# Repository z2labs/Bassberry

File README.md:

<p align="center">
  <b>A pocketable hi-fi 2.1 Bluetooth / Wi-Fi speaker built around any Raspberry Pi.</b><br>
  Cheap, easy-to-source parts · 3S 18650 battery from recycled cells · 3D-printed acoustic enclosure · fully open source
</p>

> **Status: rev 0.2 hardware in progress.** Acoustic design and simulation done. KiCad 10 schematic complete, with a HAT+ ID EEPROM so the Pi recognises the board. PCB placed by function and routed with srouter. A 4-layer digital twin verifies it against the datasheets. See [`hardware/`](hardware/).
> Everything here will change - issues and ideas are very welcome.

---

## Why

Raspberry Pi speaker HATs are either tiny mono buzzers or bare amplifier boards that leave the hard part to you: drivers, enclosure, power, battery.
Bassberry is the whole thing: a motherboard the Pi plugs into **upside down**, a DSP class-D 2.1 amplifier, USB-C PD charging, a clip-in 3S 18650 pack, and a simulated acoustic enclosure you can print at home.

It is the successor of [rfsparkling/RPi_Speaker](https://github.com/rfsparkling/RPi_Speaker) (an LM386 + GPIO-PWM board from 2016), redone properly.

## Highlights

| | |
|---|---|
| **Audio** | 2.1 channel, I2S digital all the way, 2× TI TAS5805M class-D with on-chip DSP (EQ, crossover, DRC) |
| **Drivers** | 2× 2" full-range satellites (sealed) + 1× 3.5" long-throw sub, down-firing, with 2 opposed passive radiators |
| **Response** | f₋₃ ≈ **64 Hz**, ±0.8 dB 100 Hz – 1 kHz (simulated, with DSP) |
| **Output** | ≈ **85 dB** broadband, **87 dB** @ 100 Hz, **94–97 dB** midrange @ 1 m (simulated) |
| **Host** | Every 40-pin Raspberry Pi: 1 A+/B+, 2, 3, 4, 5, Zero / Zero W / Zero 2 W - detected as a **HAT+** (ID EEPROM loads the overlay) |
| **Cooling** | Pi mounted upside down; SoC sits on an aluminium pedestal + gap pad into a 4-layer GND via field. No fan. |
| **Power** | USB-C PD in (5–20 V), 3S Li-ion buck-boost charging, 5.1 V / 5 A for the Pi, optional 18 V rail for the sub amp |
| **Battery** | 3× 18650 in snap-in holders with spring metal contacts - new or harvested cells, with balancing and reverse-cell indication |
| **UI** | 1.3" I2C OLED, power / BT / play / vol− / vol+ buttons, rotary encoder for menus (internet radio, EQ, sources) |
| **Size** | 230 × 120 × 140 mm |

## Renders

| Exterior | Rear (passive radiator, ports) |
|---|---|
|  |  |
| **Interior: acoustic chambers** | **Exploded** |
|  |  |
| **Top controls** | **Motherboard: upside-down Pi + 3S pack** |
|  |  |

Renders are generated from code with Blender Cycles: [`render/render.py`](render/render.py).

### PCB rev 0.2 (KiCad 10, routed with srouter)

| Top (Pi socket face-down, 3× 18650, lid controls) | Bottom (amplifiers, charger, buck, supervisor) |
|---|---|
|  |  |

180 × 110 mm, 4 layers. DRC 0 errors / 0 unconnected / 0 schematic-parity issues; digital twin layers 1-4 all PASS
(netlist vs datasheets, Pi plugged in face-down, copper ampacity incl. pours and vias, mechanics). Details in
[`hardware/README.md`](hardware/README.md).
Orange = sealed satellite chambers (0.20 l each), green = sub chamber (1.5 l) tuned by two opposed passive radiators.

## Acoustics

* **Satellites:** 2× 2" full-range (reference: Dayton CE54N-4) in 0.20 l sealed chambers, crossed at 180 Hz LR4.
* **Sub:** 3.5" long-throw (reference: Dayton ND91-4, Xmax 4.6 mm), down-firing, 1.5 l, with 2× 2.5" passive radiators on the side walls facing each other, so their momentum cancels and the box does not walk at high bass. Tuned to 57 Hz.
* **DSP (in the TAS5805M):** LR4 crossover, Linkwitz transform on the satellites, baffle-step compensation, subsonic filter, bass EQ, dynamic range control.
* Full lumped-element model, max-SPL / excursion limits and a driver comparison: [`docs/acoustics.md`](docs/acoustics.md) and [`acoustics/`](acoustics/).
  Plug in your own driver's T/S parameters and re-run in seconds.

## Architecture

```mermaid
flowchart LR
  USBC["USB-C PD<br/>5-20 V"] --> CHG["PD sink + 3S<br/>buck-boost charger"]
  CHG <--> BAT["3S 18650<br/>clip-in pack + BMS"]
  BAT --> BUCK["5.1 V / 5 A buck"] --> PI["Raspberry Pi<br/>(upside down)"]
  BAT --> AMP1["TAS5805M #1<br/>stereo BTL"]
  BAT --> BOOST["18 V boost<br/>(optional)"] --> AMP2["TAS5805M #2<br/>sub PBTL"]
  PI -- I2S --> AMP1 & AMP2
  PI -- I2C --> AMP1 & AMP2 & OLED["1.3&quot; OLED"]
  MCU["Supervisor MCU<br/>buttons · encoder · power latch"] -- I2C/IRQ --> PI
  MCU --> CHG
  AMP1 --> SAT["2× 2&quot; satellites"]
  AMP2 --> SUB["3.5&quot; sub + 2× PR"]
  USBC -- D+/D− --> UART["USB-UART"] --> PI
```

Details, pinout plan and power budget: [`docs/architecture.md`](docs/architecture.md).

## Built from cheap, common parts

The design rule is simple: **everything should be orderable from LCSC / AliExpress / your local electronics shop**, no exotic parts.
Amplifiers, charger, supervisor MCU, OLED, encoder and battery clips are all mass-market parts. Drivers come in two tiers:
reference drivers with published Thiele-Small data (what the simulation uses), or generic drivers that fit the same footprints, which you can measure and drop into the model.
See [`docs/bom.md`](docs/bom.md).

## Battery: recycled cells welcome

The pack is three 18650 cells in snap-in metal clips, so you can use new cells or ones harvested from old laptop packs.
Please read [`docs/battery.md`](docs/battery.md) first: matching, testing and the protections on the board.

## Roadmap

- [x] Concept, architecture, acoustic design and simulation
- [x] Schematic (KiCad 10, generated from [`hardware/tools`](hardware/tools))
- [ ] PCB layout, 4-layer, Pi thermal pedestal (rev 0.2: placed + routed, DRC / twin closure in progress)
- [ ] 3D-printable enclosure (STEP + STL), gaskets, damping
- [ ] Linux: dual TAS5805M 2.1 sound card, DSP profiles, supervisor daemon, OLED menu
- [ ] Prototype measurements vs simulation
- [ ] Build guide

## Repository layout

```
acoustics/   lumped-element simulation, plots, driver comparison
docs/        architecture, acoustics, BOM, battery guide, images
render/      Blender (bpy) script that generates the renders
tools/       helper scripts (banner, ...)
hardware/    KiCad 10 project + Python generators
enclosure/   CAD / STL (coming)
software/    Linux drivers, DSP profiles, UI (coming)
```

## License

* Hardware (`hardware/`, `enclosure/`): [CERN-OHL-S-2.0](LICENSES/CERN-OHL-S-2.0.txt)
* Software and scripts: [MIT](LICENSES/MIT.txt)
* Documentation and images: [CC-BY-SA-4.0](LICENSES/CC-BY-SA-4.0.txt)

Made by [Z2Labs](https://github.com/z2labs) in Budapest.

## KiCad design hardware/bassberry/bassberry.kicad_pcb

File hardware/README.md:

# Hardware - Bassberry motherboard (KiCad 10)

**Status: rev 0.2 (branch `feat/rev02-layout`) - HAT+ EEPROM, back-power diode, 18650 holders, functional placement, srouter routing, digital twin.**

Open `bassberry/bassberry.kicad_pro` in KiCad 10. A PDF of the schematic is in [`bassberry/bassberry_sch.pdf`](bassberry/bassberry_sch.pdf).

## Sheets

| Sheet | Content |
|---|---|
| `pi.kicad_sch` | 40-pin socket for a **face-down** Raspberry Pi (B+/2/3/4/5/Zero), I2S series termination, HAT+ ID EEPROM (CAT24C32 @ 0x50, WP jumper), back-power ideal diode |
| `audio.kicad_sch` | 2x TI TAS5805M: U201 stereo BTL (satellites, PVDD = VBAT), U202 PBTL (sub, PVDD_SUB), LC output filters, speaker connectors |
| `power.kicad_sch` | USB-C, Injoinic IP2366 PD3.1 3S buck-boost charger (30 W, 4.2 V/cell), TPS565208 5.1 V / 5 A Pi buck, optional MT3608 ~17 V sub boost, HT7533 LDOs |
| `battery.kicad_sch` | 3x 18650 in MYOUNG BH-18650-B1BA002 SMT holders (Keystone 1042 clone), off-the-shelf 3S BMS module (B-, B1, B2, B+, P-), reverse-cell LEDs, 10 A fuse, NTC |
| `ui.kicad_sch` | CH32V003 supervisor (power latch, buttons, encoder, VBAT sense, I2C slave to the Pi), OLED header, CH340C USB console |

Reference designators are numbered per sheet: 1xx Pi, 2xx audio, 3xx power, 4xx battery, 5xx UI.

## Board

* 180 x 110 mm, 4 layers, 1.6 mm. Layer roles as in srouter's rev-B3 flow: **F.Cu** signals + GND pour, **In1.Cu** signals
  (power stays on the outer layers), **In2.Cu** solid GND, **B.Cu** parts + signals + GND pour. Netclass 0.15 mm / 0.2 mm, via 0.6/0.3 mm.
* Top: face-down Pi (fitted to the Pi 4/5 hole pattern, ports over the open rear-left corner), three 18650 holders front-to-back
  with alternating polarity (series links 20 mm), USB-C at the rear, buttons / EC11 encoder / OLED socket in the front strip.
* Bottom: every other part, placed by function: each passive next to the pin it serves (`pcb_build.py`).
* Pi SoC thermal pad: covers the Pi 4 **and** the Pi 5 SoC lid (from the mechanical drawings), exposed copper both sides,
  0.3 mm GND via field, two M2.5 bolts for the aluminium pedestal. Copper keep-out under the Pi 4/5 Wi-Fi antenna corner.

## Regenerating (Windows, KiCad 10)

```powershell
powershell -File hardware\tools\regen_sch.ps1                       # schematic, ERC, netlist
& $py hardware\tools\pcb_build.py                                   # outline, placement, zones -> bassberry_placed.kicad_pcb
& $py hardware\tools\route.py                                       # srouter: escape gate, trunks + 3 passes, fatten
powershell -File hardware\tools\postroute.ps1                       # track_tidy, fill, gnd_stitch, via_rescue, stitch_audit,
                                                                     # silk_dfm, DRC --schematic-parity, digital twin 1-4
```

Routing follows `srouter/docs/USAGE.md`: GND is never routed (In2 plane + F/B pours, stitched afterwards).
* **Pass 0 (trunks)** - srouter gives a net one width that must fit its smallest pad, so a battery rail that also touches a
  0.3 mm amplifier pin would be 0.2 mm end to end. `route.py` therefore splits each high-current net on a scratch copy:
  the small pads go to a dummy net, and srouter joins only the big pads (holders, fuse, 2512 links, inductors, MOSFET tabs,
  connectors) at the widest width they allow (up to 1.6 mm). The later passes join the small pads to that trunk at their own
  width: the neck-down happens only in the last millimetres before a fine-pitch pin.
* **Pass 1a** - the rest of the high-current nets alone, on the outer copper only (In1 closed: 0.5 oz inner copper would need 3x the
  width), vias strongly avoided. srouter routes a net with one width that has to fit its smallest pad, so `fatten.py` then
  widens that copper wherever the clearance allows (necking only next to small pads, keeping a 0.5 mm escape lane around
  every foreign pad) and adds parallel vias at its layer changes.
* **Pass 1b** - everything that escapes from between power pins (the IP2366 QFN, the amp bootstrap pins) and the 3V3 rails.
* **Pass 2** - I2S, I2C, USB D+/D- (crossover under the receptacle pre-routed), HAT ID, every other Pi header net.
* **Pass 3** - the rest.
* **Post** (`postroute.ps1`, the USAGE.md order): track_tidy, `power_pour.py` (a priority-5 copper pour hugging every
  high-current track on F.Cu, In1.Cu and B.Cu, filled only into free space, plus ceil(I / 1.5 A) parallel vias at every
  layer change of a high-current net), zone fill, gnd_stitch, via_rescue, stitch_audit, silk_dfm, zone refill, DRC with
  schematic parity, digital twin 1-4. `full_flow.ps1` runs everything unattended.
* Gates: `escape_probe.py` (no pad walled in before routing), the pre-route twin layers 1/2/4; `full_flow.ps1` stops on any failure.
* Repairs: `tidy_guard.py` re-joins what srouter's track_tidy pulls apart (pads, track pieces, lost layer changes) and drops dangling stubs;
  GND pins with no room for a via get one between the pin rows (0.45/0.2 mm) or a short link to the nearest GND.

## Digital twin

`hardware/twin/` - four layers, spec written only from datasheets and the Raspberry Pi documents, each with injected-fault
self-tests. See [`twin/README.md`](twin/README.md).

## Result (rev 0.2, `hardware/bassberry/route/`)

| Check | Result |
|---|---|
| ERC | 2 expected errors only (TAS5805M PBTL output pairing, as in the TI datasheet) |
| Routing | every net routed by srouter (trunk pass, 3 passes, automatic rip-up and reroute for nets left over) |
| DRC (`--schematic-parity --severity-all`) | **0 errors, 0 unconnected, 0 parity**; 152 warnings: 122 `lib_footprint_mismatch` (silk_dfm moved/cut silkscreen inside the footprints), 29 silkscreen cosmetics, 1 copper sliver |
| Twin layer 1 (netlist vs source documents) | 170 PASS, 10 WARN (physical checks + accepted deviations), 0 FAIL; 16/16 injected faults caught |
| Twin layer 2 (Pi 4/5 plugged in face-down) | 7 + 31 PASS; 2/2 injected faults caught |
| Twin layer 3 (copper ampacity, set-points, LDO) | 36 PASS, 0 FAIL; 2/2 injected faults caught |
| Twin layer 4 (mechanics) | 37 PASS; 4/4 injected faults caught |

How the power copper was made to pass layer 3 (all automatic, `power_pour.py`): corridor pours per high-current net on
F.Cu / In1.Cu / B.Cu splitting the room between neighbouring nets, a **+BATT plane on In1.Cu** fed by taps from every
+BATT pad, In1 copies of the battery-link pours (joined by the holder through-hole contacts), and vias grown to 1.0/0.5 mm
or doubled until each layer change carries its current. The buck converter is turned so its SW pin points straight at the
inductor, the ZVD PFET so its source pins face the Pi 5 V pins.

## Known open items (rev 0.2)

- [ ] ERC: 2 expected errors - TAS5805M PBTL pre-filter output pairing (OUT_A+/OUT_A-, OUT_B+/OUT_B-), exactly as in TI's datasheet fig. "MONO (PBTL) Systems".
- [ ] Confirm the Pi antenna keep-out on a real Pi 4 / Pi 5 / Pi 3B+.
- [ ] CH340C supply current from the current WCH datasheet (the LDO dissipation check at a 20 V PD contract uses 15 mA).
- [ ] TDSON MOSFETs: pick the final cheap part (30-40 V, ~5 mOhm, JEDEC SO-8FL pin-out).
- [ ] Device tree overlay and DSP profiles (`software/overlay`, draft).

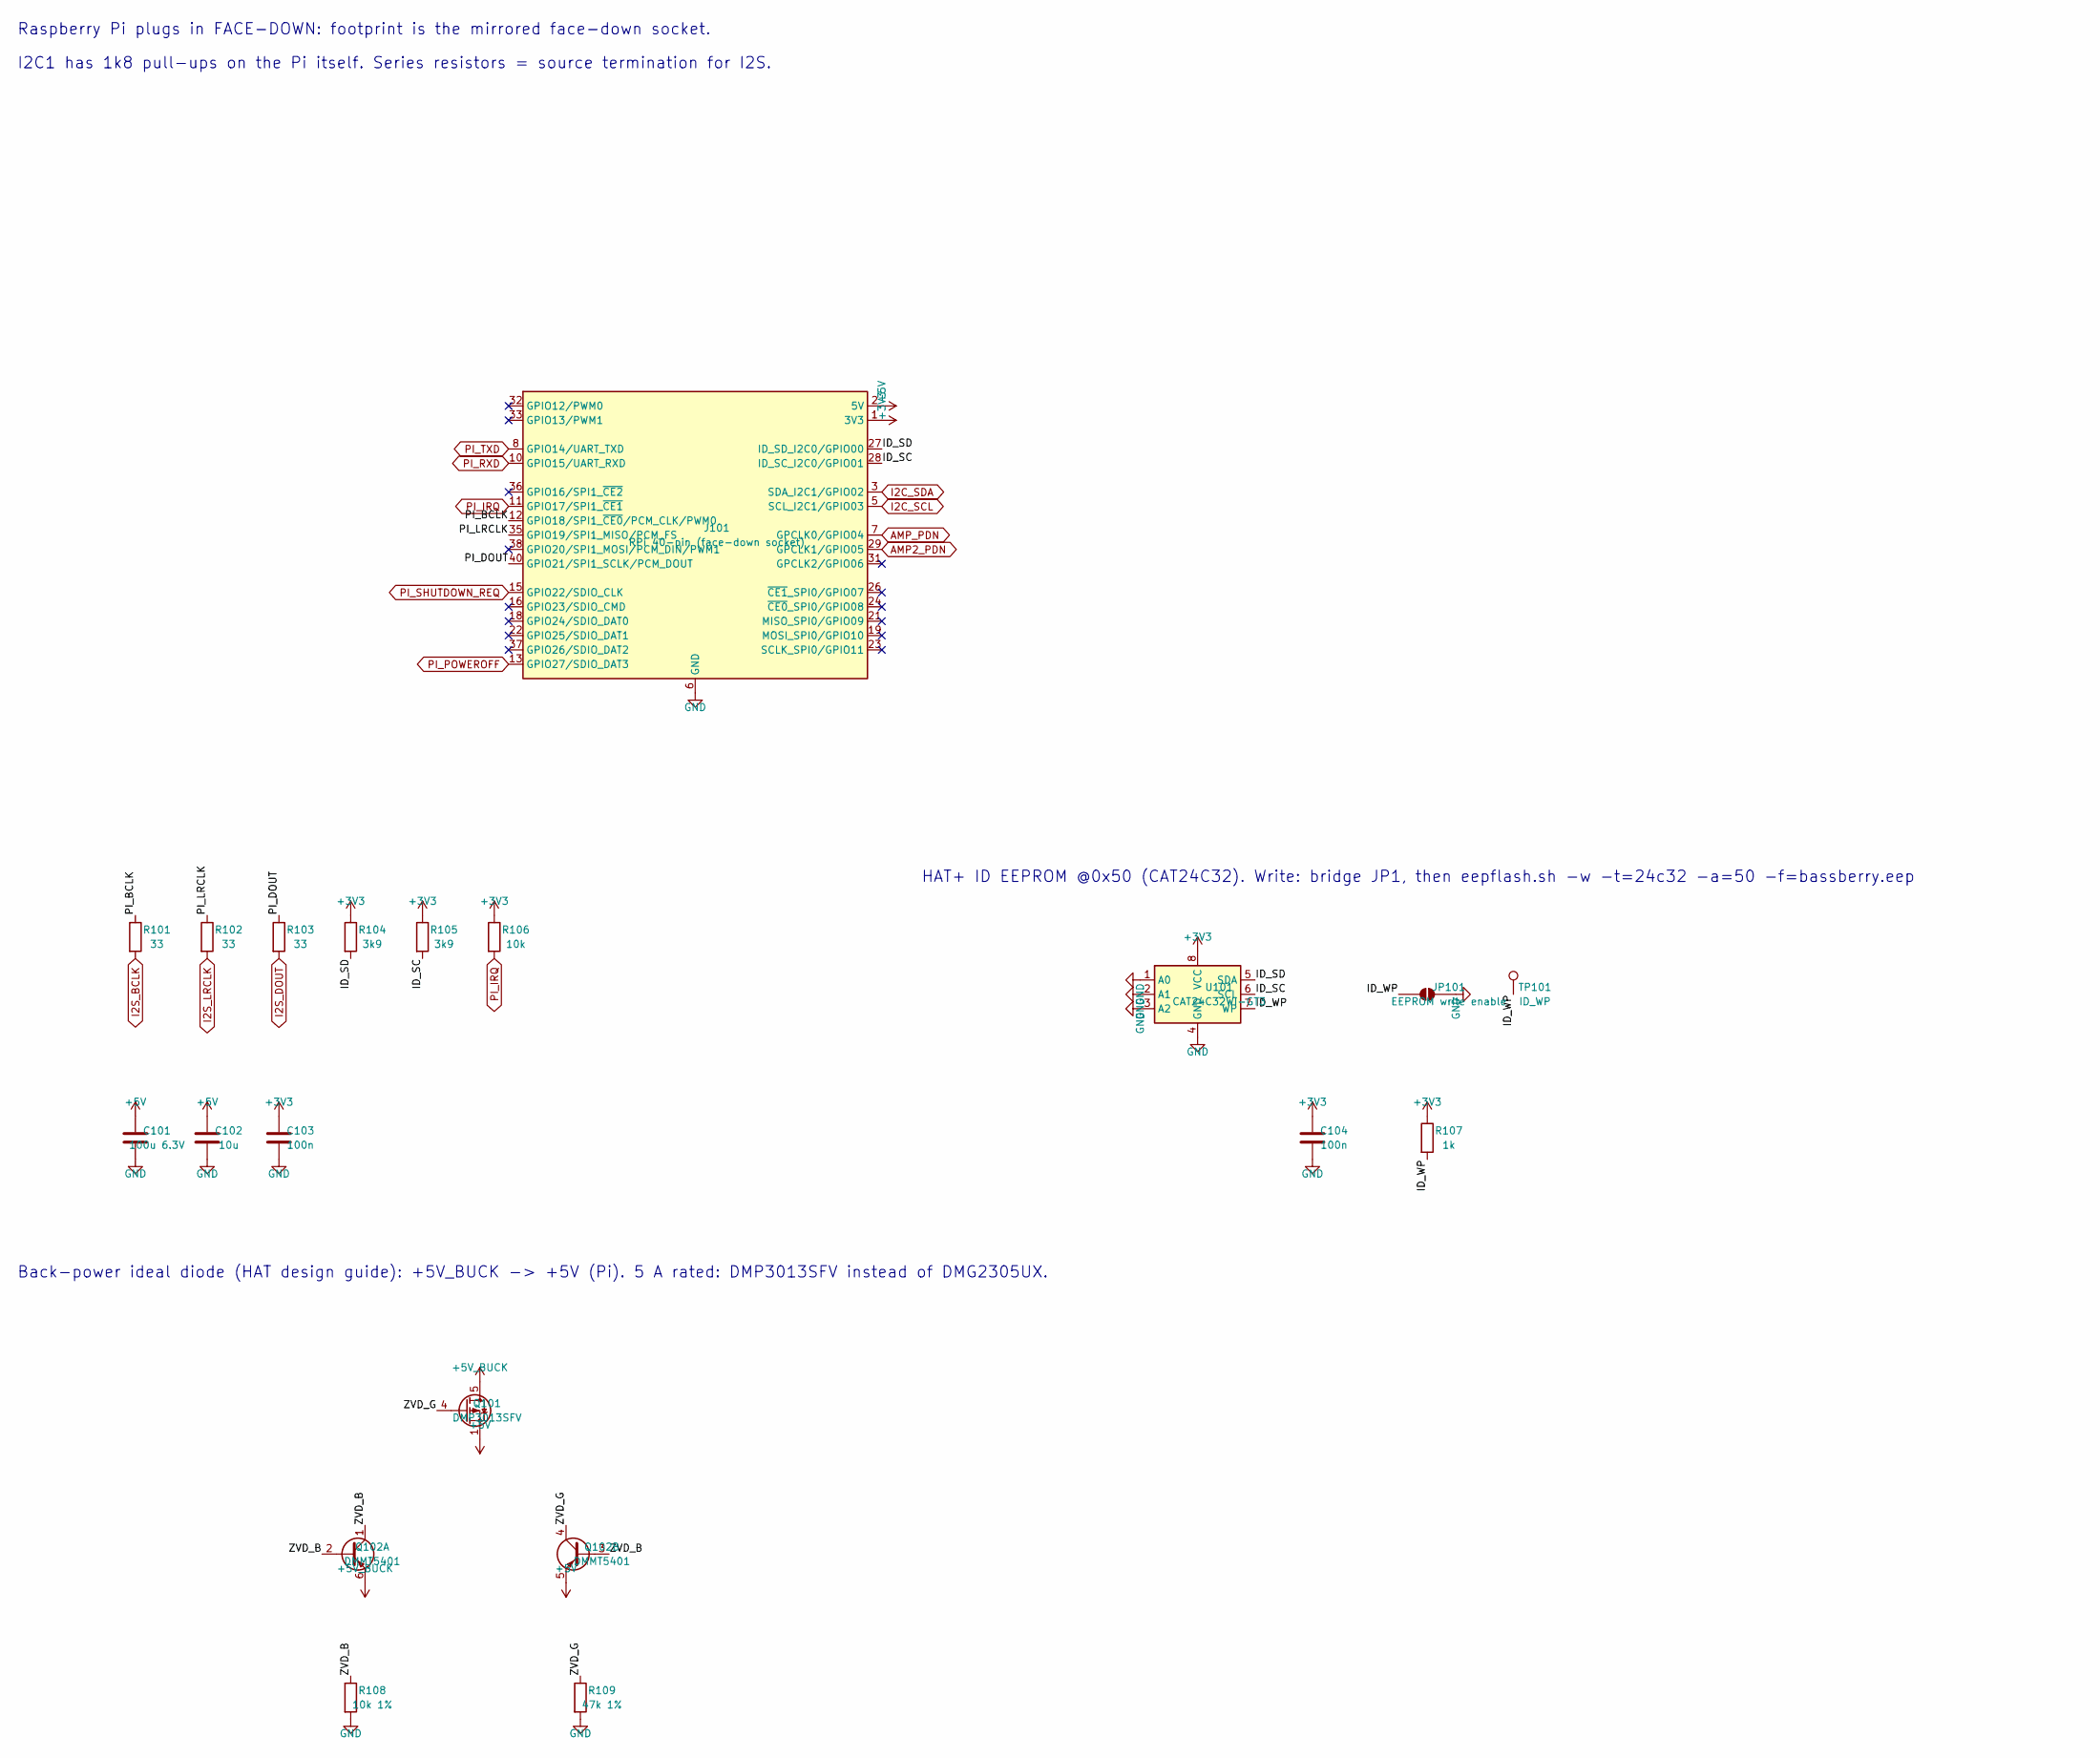
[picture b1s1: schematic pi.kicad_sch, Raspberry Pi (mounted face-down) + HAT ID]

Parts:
C101: 100u 6.3V; C_1210_3225Metric
C102: 10u; C_0805_2012Metric
C103, C104: 100n; C_0603_1608Metric
J101: RPi 40-pin (face-down socket); Raspberry_Pi_Zero_Socketed_THT_FaceDown_MountingHoles
JP101: EEPROM write enable; SolderJumper-2_P1.3mm_Open_RoundedPad1.0x1.5mm
Q101: DMP3013SFV; Diodes_PowerDI3333-8
Q102: DMMT5401; SOT-23-6
R101, R102, R103: 33; R_0603_1608Metric
R104, R105: 3k9; R_0603_1608Metric
R106: 10k; R_0603_1608Metric
R107: 1k; R_0603_1608Metric
R108: 10k 1%; R_0603_1608Metric
R109: 47k 1%; R_0603_1608Metric
TP101: ID_WP; TestPoint_Pad_D1.5mm
U101: CAT24C32WI-GT3; SOIC-8_3.9x4.9mm_P1.27mm

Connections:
+3V3: C103.1, C104.1, J101.1 (3V3), J101.17 (3V3), R104.1, R105.1, R106.1, R107.1, U101.8 (VCC); also elsewhere on the board
+5V: C101.1, C102.1, J101.2 (5V), J101.4 (5V), Q101.1 (S), Q101.2 (S), Q101.3 (S), Q102.5 (E2)
+5V_BUCK: Q101.5 (D), Q102.6 (E1); also elsewhere on the board
/pi/ID_SC: J101.28 (ID_SC_I2C0/GPIO01), R105.2, U101.6 (SCL)
/pi/ID_SD: J101.27 (ID_SD_I2C0/GPIO00), R104.2, U101.5 (SDA)
/pi/ID_WP: JP101.1 (A), R107.2, TP101.1, U101.7 (WP)
/pi/PI_BCLK: J101.12 (GPIO18/SPI1_~CE0/PCM_CLK/PWM0), R101.1
/pi/PI_DOUT: J101.40 (GPIO21/SPI1_SCLK/PCM_DOUT), R103.1
/pi/PI_LRCLK: J101.35 (GPIO19/SPI1_MISO/PCM_FS), R102.1
/pi/ZVD_B: Q102.1 (C1), Q102.2 (B1), Q102.3 (B2), R108.1
/pi/ZVD_G: Q101.4 (G), Q102.4 (C2), R109.1
AMP2_PDN: J101.29 (GPCLK1/GPIO05); also elsewhere on the board
AMP_PDN: J101.7 (GPCLK0/GPIO04); also elsewhere on the board
GND: C101.2, C102.2, C103.2, C104.2, J101.6 (GND), J101.9 (GND), J101.14 (GND), J101.20 (GND), J101.25 (GND), J101.30 (GND), J101.34 (GND), J101.39 (GND), JP101.2 (B), R108.2, R109.2, U101.1 (A0), U101.2 (A1), U101.3 (A2), U101.4 (GND); also elsewhere on the board
I2C_SCL: J101.5 (SCL_I2C1/GPIO03); also elsewhere on the board
I2C_SDA: J101.3 (SDA_I2C1/GPIO02); also elsewhere on the board
I2S_BCLK: R101.2; also elsewhere on the board
I2S_DOUT: R103.2; also elsewhere on the board
I2S_LRCLK: R102.2; also elsewhere on the board
PI_IRQ: J101.11 (GPIO17/SPI1_~CE1), R106.2; also elsewhere on the board
PI_POWEROFF: J101.13 (GPIO27/SDIO_DAT3); also elsewhere on the board
PI_RXD: J101.10 (GPIO15/UART_RXD); also elsewhere on the board
PI_SHUTDOWN_REQ: J101.15 (GPIO22/SDIO_CLK); also elsewhere on the board
PI_TXD: J101.8 (GPIO14/UART_TXD); also elsewhere on the board

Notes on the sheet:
Raspberry Pi plugs in FACE-DOWN: footprint is the mirrored face-down socket.
I2C1 has 1k8 pull-ups on the Pi itself. Series resistors = source termination for I2S.
HAT+ ID EEPROM @0x50 (CAT24C32). Write: bridge JP1, then eepflash.sh -w -t=24c32 -a=50 -f=bassberry.eep
Back-power ideal diode (HAT design guide): +5V_BUCK -> +5V (Pi). 5 A rated: DMP3013SFV instead of DMG2305UX.

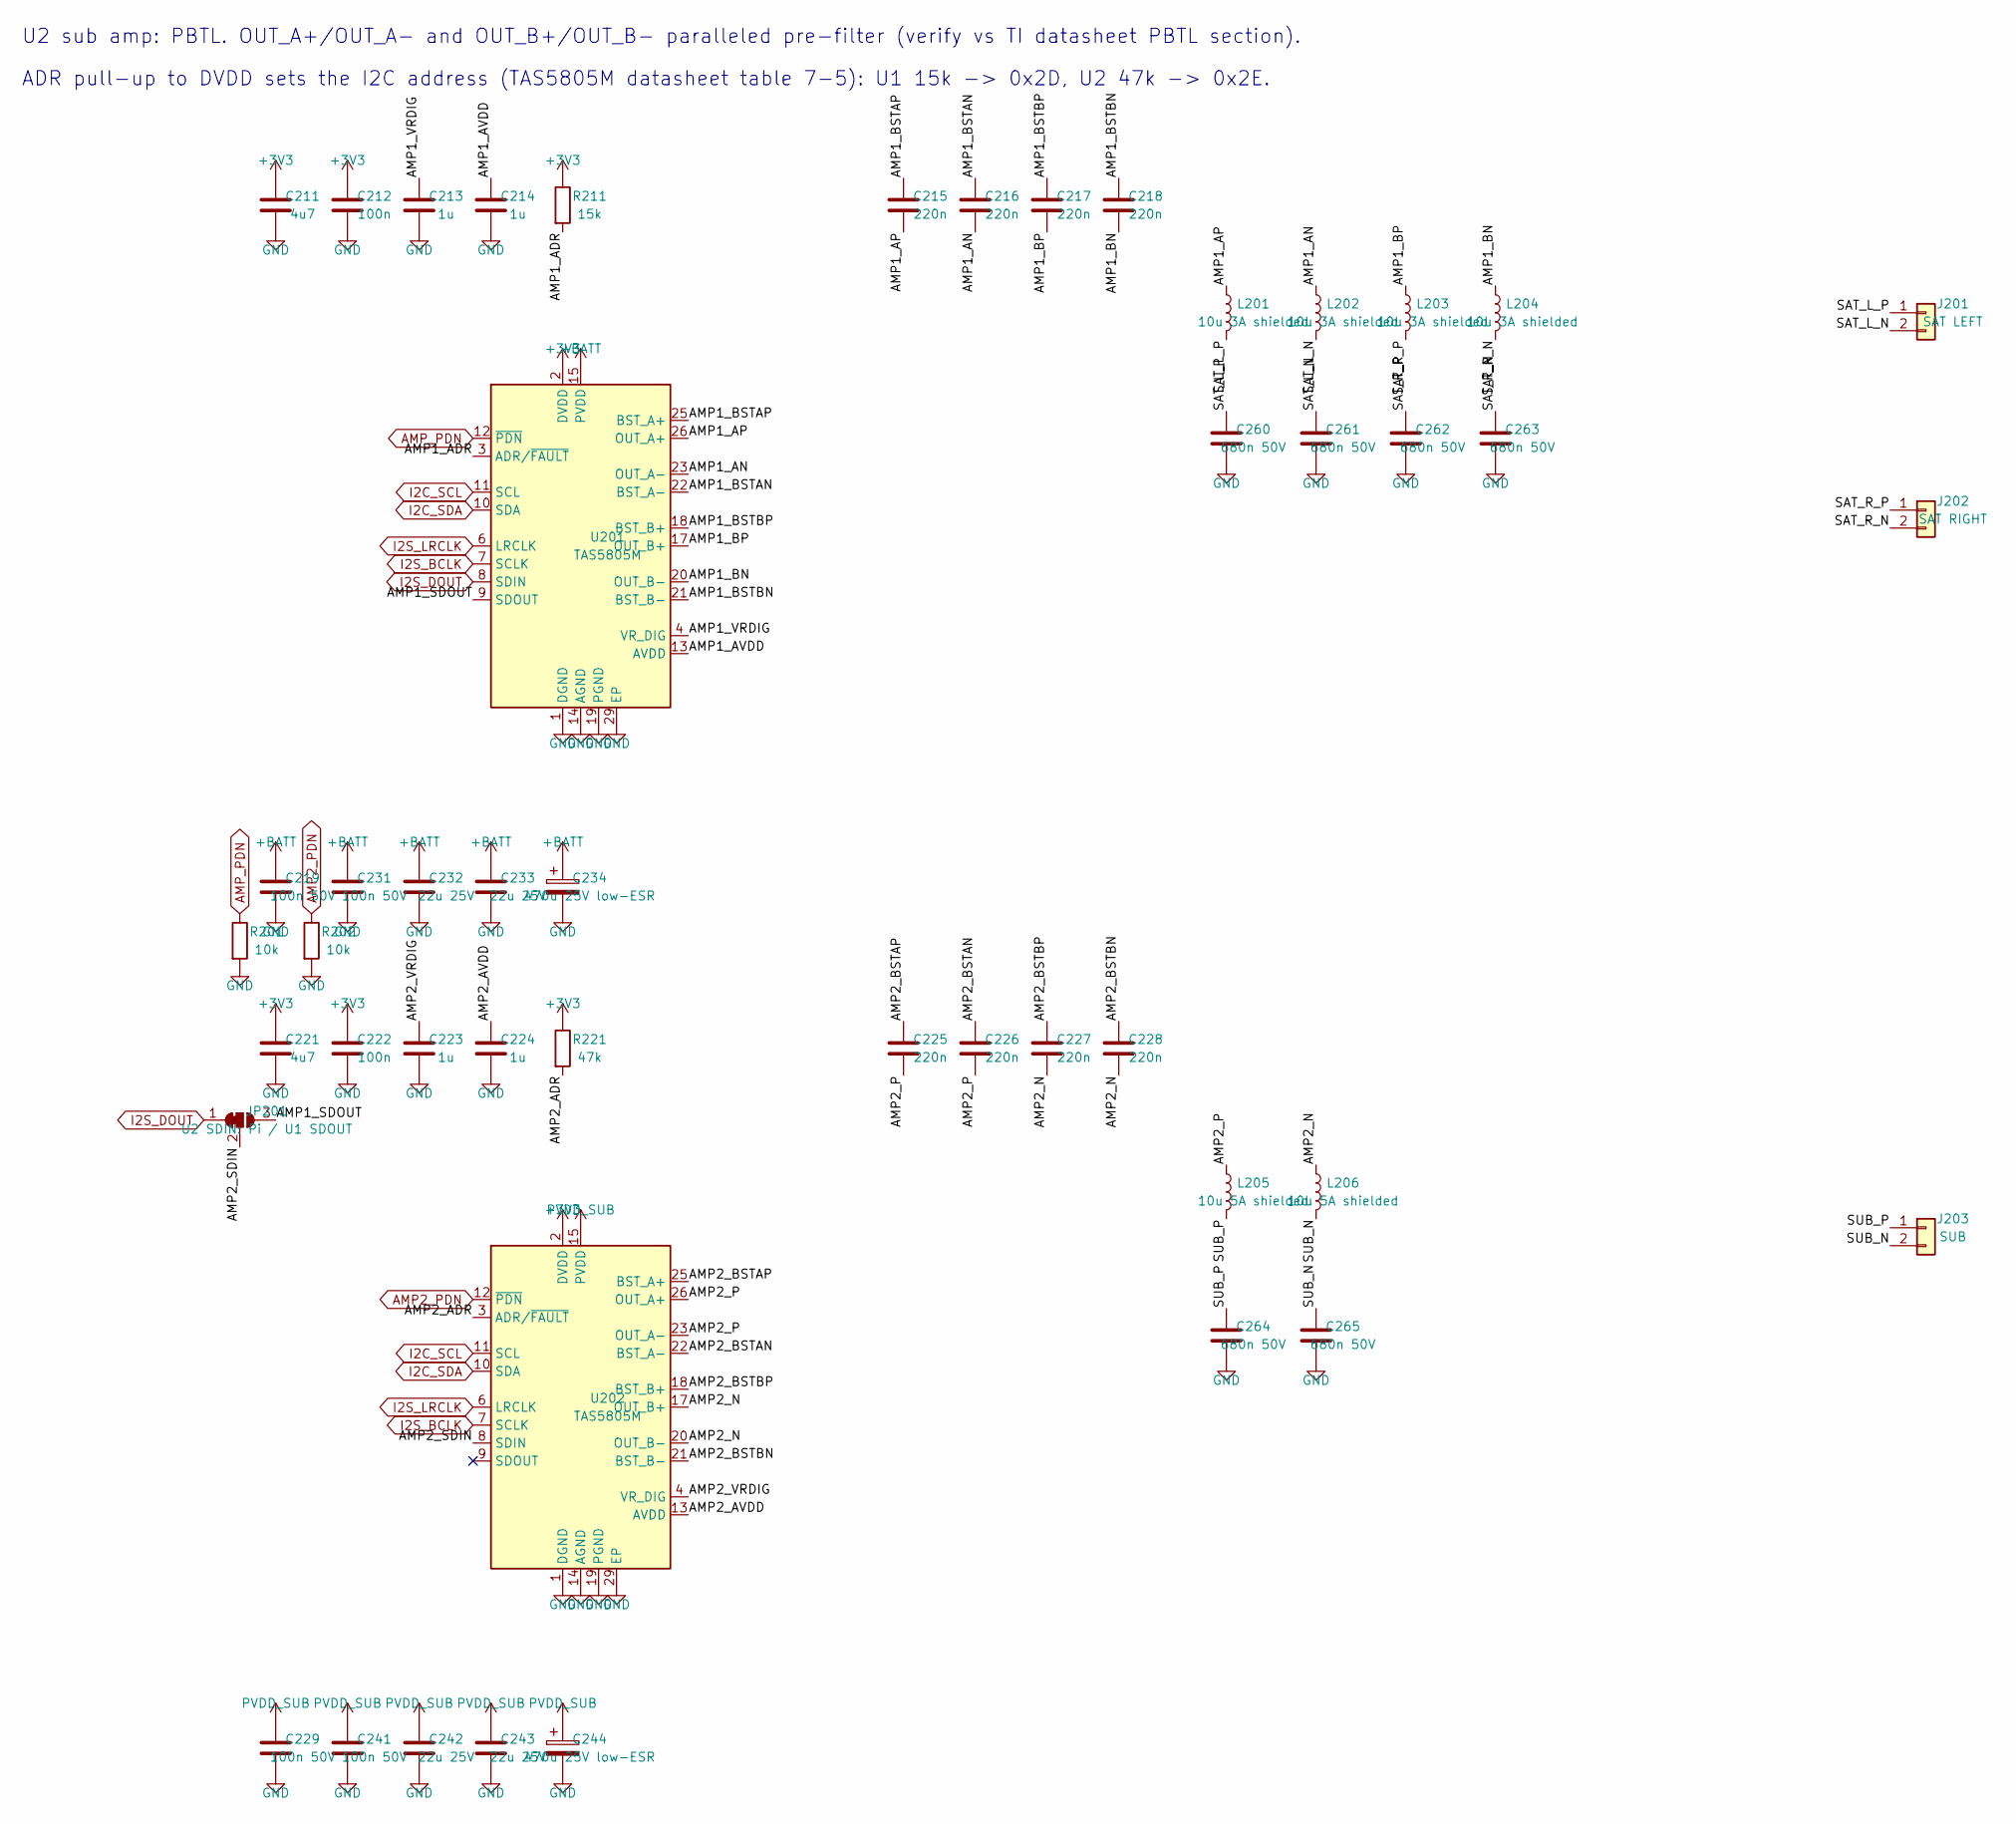
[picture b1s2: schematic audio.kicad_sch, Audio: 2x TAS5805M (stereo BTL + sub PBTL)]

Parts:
C211, C221: 4u7; C_0603_1608Metric
C212, C222: 100n; C_0603_1608Metric
C213, C214, C223, C224: 1u; C_0603_1608Metric
C215, C216, C217, C218, C225, C226, C227, C228: 220n; C_0603_1608Metric
C219, C229, C231, C241: 100n 50V; C_0603_1608Metric
C232, C233, C242, C243: 22u 25V; C_1206_3216Metric
C234, C244: 470u 25V low-ESR; CP_Elec_10x10.5
C260, C261, C262, C263, C264, C265: 680n 50V; C_0805_2012Metric
J201: SAT LEFT; JST_XH_B2B-XH-A_1x02_P2.50mm_Vertical
J202: SAT RIGHT; JST_XH_B2B-XH-A_1x02_P2.50mm_Vertical
J203: SUB; JST_XH_B2B-XH-A_1x02_P2.50mm_Vertical
JP201: U2 SDIN: Pi / U1 SDOUT; SolderJumper-3_P1.3mm_Bridged12_RoundedPad1.0x1.5mm
L201, L202, L203, L204: 10u 3A shielded; L_Changjiang_FXL1040
L205, L206: 10u 5A shielded; L_Changjiang_FXL1050
R201, R202: 10k; R_0603_1608Metric
R211: 15k; R_0603_1608Metric
R221: 47k; R_0603_1608Metric
U201, U202: TAS5805M; HTSSOP-28-1EP_4.4x9.7mm_P0.65mm_EP2.85x5.4mm_ThermalVias

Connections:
+3V3: C211.1, C212.1, C221.1, C222.1, R211.1, R221.1, U201.2 (DVDD), U202.2 (DVDD); also elsewhere on the board
+BATT: C219.1, C231.1, C232.1, C233.1, C234.1, U201.15 (PVDD), U201.16 (PVDD), U201.27 (PVDD), U201.28 (PVDD); also elsewhere on the board
/audio/AMP1_ADR: R211.2, U201.3 (ADR/~FAULT)
/audio/AMP1_AN: C216.2, L202.1, U201.23 (OUT_A-)
/audio/AMP1_AP: C215.2, L201.1, U201.26 (OUT_A+)
/audio/AMP1_AVDD: C214.1, U201.13 (AVDD)
/audio/AMP1_BN: C218.2, L204.1, U201.20 (OUT_B-)
/audio/AMP1_BP: C217.2, L203.1, U201.17 (OUT_B+)
/audio/AMP1_BSTAN: C216.1, U201.22 (BST_A-)
/audio/AMP1_BSTAP: C215.1, U201.25 (BST_A+)
/audio/AMP1_BSTBN: C218.1, U201.21 (BST_B-)
/audio/AMP1_BSTBP: C217.1, U201.18 (BST_B+)
/audio/AMP1_SDOUT: JP201.3 (B), U201.9 (SDOUT)
/audio/AMP1_VRDIG: C213.1, U201.4 (VR_DIG)
/audio/AMP2_ADR: R221.2, U202.3 (ADR/~FAULT)
/audio/AMP2_AVDD: C224.1, U202.13 (AVDD)
/audio/AMP2_BSTAN: C226.1, U202.22 (BST_A-)
/audio/AMP2_BSTAP: C225.1, U202.25 (BST_A+)
/audio/AMP2_BSTBN: C228.1, U202.21 (BST_B-)
/audio/AMP2_BSTBP: C227.1, U202.18 (BST_B+)
/audio/AMP2_N: C227.2, C228.2, L206.1, U202.17 (OUT_B+), U202.20 (OUT_B-)
/audio/AMP2_P: C225.2, C226.2, L205.1, U202.23 (OUT_A-), U202.26 (OUT_A+)
/audio/AMP2_SDIN: JP201.2 (C), U202.8 (SDIN)
/audio/AMP2_VRDIG: C223.1, U202.4 (VR_DIG)
/audio/SAT_L_N: C261.1, J201.2, L202.2
/audio/SAT_L_P: C260.1, J201.1, L201.2
/audio/SAT_R_N: C263.1, J202.2, L204.2
/audio/SAT_R_P: C262.1, J202.1, L203.2
/audio/SUB_N: C265.1, J203.2, L206.2
/audio/SUB_P: C264.1, J203.1, L205.2
AMP2_PDN: R202.1, U202.12 (~PDN); also elsewhere on the board
AMP_PDN: R201.1, U201.12 (~PDN); also elsewhere on the board
GND: C211.2, C212.2, C213.2, C214.2, C219.2, C221.2, C222.2, C223.2, C224.2, C229.2, C231.2, C232.2, C233.2, C234.2, C241.2, C242.2, C243.2, C244.2, C260.2, C261.2, C262.2, C263.2, C264.2, C265.2, R201.2, R202.2, U201.1 (DGND), U201.5 (DGND), U201.14 (AGND), U201.19 (PGND), U201.24 (PGND), U201.29 (EP), U202.1 (DGND), U202.5 (DGND), U202.14 (AGND), U202.19 (PGND), U202.24 (PGND), U202.29 (EP); also elsewhere on the board
I2C_SCL: U201.11 (SCL), U202.11 (SCL); also elsewhere on the board
I2C_SDA: U201.10 (SDA), U202.10 (SDA); also elsewhere on the board
I2S_BCLK: U201.7 (SCLK), U202.7 (SCLK); also elsewhere on the board
I2S_DOUT: JP201.1 (A), U201.8 (SDIN); also elsewhere on the board
I2S_LRCLK: U201.6 (LRCLK), U202.6 (LRCLK); also elsewhere on the board
PVDD_SUB: C229.1, C241.1, C242.1, C243.1, C244.1, U202.15 (PVDD), U202.16 (PVDD), U202.27 (PVDD), U202.28 (PVDD); also elsewhere on the board

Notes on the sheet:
U2 sub amp: PBTL. OUT_A+/OUT_A- and OUT_B+/OUT_B- paralleled pre-filter (verify vs TI datasheet PBTL section).
ADR pull-up to DVDD sets the I2C address (TAS5805M datasheet table 7-5): U1 15k -> 0x2D, U2 47k -> 0x2E.

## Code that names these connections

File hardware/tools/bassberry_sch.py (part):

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    {"26": "AMP1_AP", "23": "AMP1_AN", "17": "AMP1_BP", "20": "AMP1_BN"}, "AMP_PDN")
tas(au, "U2", 2, 110, 215, "PVDD_SUB", "47k", "AMP2_SDIN", "NC",
    {"26": "AMP2_P", "23": "AMP2_P", "17": "AMP2_N", "20": "AMP2_N"}, "AMP2_PDN")
# PDN pull-downs: amps stay in shutdown until the Linux driver (one PDN GPIO per codec: GPIO4, GPIO5) wakes them
au.R("R1", "10k", 60, 150, "AMP_PDN", "GND", R0603)
au.R("R2", "10k", 72, 150, "AMP2_PDN", "GND", R0603)
au.part("Jumper:SolderJumper_3_Bridged12", "JP1", "U2 SDIN: Pi / U1 SDOUT", 60, 175,
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pw.part("bassberry:IP2366", "U2", "IP2366", 170, 120, fp="Package_DFN_QFN:QFN-40-1EP_5x5mm_P0.4mm_EP3.6x3.6mm_ThermalVias",
        nets={"VBUS": "VBUS", "VBUSG": "CHG_VBUSG", "VBUSI": "CHG_VIN", "VIO": "CHG_VIN", "CSP1": "CHG_VIN",
              "CSN1": "CHG_CSN1", "PCIN": "CHG_NODEB", "CC1": "CC1", "CC2": "CC2", "DPC": "NC", "DMC": "NC",
              "EN": "CHG_EN", "GPIO20": "CHG_LED_A_R", "GPIO19": "CHG_LED_B_R", "GPIO1": "CHG_LED_COM",
              "HG1": "CHG_HG1_R", "BST1": "CHG_BST1", "LX1": "CHG_LX1", "LG1": "CHG_LG1_R", "LG2": "CHG_LG2_R",
              "LX2": "CHG_LX2", "BST2": "CHG_BST2", "HG2": "CHG_HG2_R", "PCON": "CHG_NODEC", "CSN2": "CHG_CSN2",
              "CSP2": "+BATT", "BAT": "+BATT", "CC_BDO": "CHG_CCBDO", "VCC5V": "CHG_VCC5V", "VCCIO": "CHG_VCCIO",
              "GPIO4/BAT_NUM": "CHG_BATNUM", "GPIO3/PSET": "CHG_PSET", "GPIO2/VSET": "CHG_VSET", "GPIO0/NTC": "NTC",
              "AGND": "GND", "EPAD": "GND"})
r = Row(pw, 115, 200, 10.16)
r.R("R1", "51", "CHG_NODEB", "CHG_CSN1", R0603)
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
# =====================================================================  UI / supervisor / console
ui = P.child("ui", "ui.kicad_sch", "UI + supervisor MCU (CH32V003), OLED, buttons, encoder, USB console", GLOBAL)
ui.text("Supervisor runs from +3V3_AON. I2C slave to the Pi on PC1/PC2; PI_IRQ and PI_SHUTDOWN_REQ are open-drain.", 25, 22)
ui.text("Buttons active-low with MCU internal pull-ups. VBAT_SENSE = VBAT * 22/122.", 25, 28)
ui.part("MCU_WCH_RiscV:CH32V003FxPx", "U1", "CH32V003F4P6", 110, 100, fp="Package_SO:TSSOP-20_4.4x6.5mm_P0.65mm",
        nets={"VDD": "+3V3_AON", "VSS": "GND", "PC0": "BOOST_EN", "PC1": "I2C_SDA", "PC2": "I2C_SCL",
              "PC3": "BTN_PWR", "PC4": "BTN_BT", "PC5": "BTN_PLAY", "PC6": "BTN_VOLDN", "PC7": "BTN_VOLUP",
              "PD0": "PI_POWEROFF", "PD1": "SWIO", "PD2": "ENC_A", "PD3": "ENC_B", "PD4": "ENC_SW",
              "PD5": "PI_IRQ", "PD6": "PI_SHUTDOWN_REQ", "PD7": "MCU_NRST", "PA1": "PI_PWR_EN", "PA2": "VBAT_SENSE"})
r = Row(ui, 60, 150, 10.16)
r.C("C1", "100n", "+3V3_AON", "GND", C0603)
r.C("C2", "1u", "+3V3_AON", "GND", C0603)
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r.R("R2", "100k 1%", "+BATT", "VBAT_SENSE", R0603)
r.R("R3", "22k 1%", "VBAT_SENSE", "GND", R0603)
r.C("C3", "100n", "VBAT_SENSE", "GND", C0603)
ui.part("Connector_Generic:Conn_01x03", "J1", "SWIO (WCH-LinkE)", 200, 150, fp="Connector_PinHeader_2.54mm:PinHeader_1x03_P2.54mm_Vertical",
        nets={"1": "+3V3_AON", "2": "SWIO", "3": "GND"})
for i, (net, name) in enumerate((("BTN_PWR", "POWER"), ("BTN_BT", "BT"), ("BTN_PLAY", "PLAY/PAUSE"), ("BTN_VOLDN", "VOL-"), ("BTN_VOLUP", "VOL+"))):
    ui.part("Switch:SW_Push", f"SW{i+1}", name, 210, 60 + i * 12.7, fp="Button_Switch_SMD:SW_SPST_TL3342", nets={"1": net, "2": "GND"})
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
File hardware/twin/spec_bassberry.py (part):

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The PDFs live in hardware/_datasheets (not in git: copyright); URLs below.

Sources
  [RPI-SCH]   Raspberry Pi 4 Model B reduced schematics, J8 (40-pin header): pin -> GPIO / power / ID_SD / ID_SC,
              (SDA1)(SCL1)(TXD0)(RXD0) labels.  https://datasheets.raspberrypi.com/rpi4/raspberry-pi-4-reduced-schematics.pdf
  [BCM2711]   BCM2711 ARM Peripherals, 5.3 alternative function table: GPIO18 PCM_CLK, GPIO19 PCM_FS, GPIO21 PCM_DOUT (ALT0).
              https://datasheets.raspberrypi.com/bcm2711/bcm2711-peripherals.pdf
  [RPI-MECH]  Raspberry Pi 4 / Pi 5 mechanical drawings (85 x 56 mm, holes 58 x 49 at 3.5 mm, header centre 29 mm from
              the hole, Pi 4 SoC 25.75 / 32.5 mm, Pi 5 drawing: pin 1 = square pad, inner row, end away from the ports).
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  [DS-MT3608] Aerosemi MT3608, pin description (1 SW, 2 GND, 3 FB, 4 EN, 5 IN, 6 NC), VFB = 0.6 V, SW max 28 V.
  [DS-DMP]    Diodes DMP3013SFV, PowerDI3333-8: pins 1-3 S, 4 G, 5-8 D (bottom view), 17 mOhm @ -4.5 V.
  [DS-DMMT]   Diodes DMMT5401 SOT26 top view: 1 C1, 2 B1, 3 B2, 4 C2, 5 E2, 6 E1.
  [DS-CH32]   WCH CH32V003 datasheet V1.1, Table 2-1 (TSSOP20 column): 1 PD4 .. 20 PD3, 7 VSS, 9 VDD; PC1 SDA, PC2 SCL, PD1 SWIO.
  [DS-CH340]  WCH CH340DS1 V3: CH340C SOP16: 1 GND, 2 TXD, 3 RXD, 4 V3, 5 UD+, 6 UD-, 15 R232, 16 VCC; V3 = VCC for 3.3 V.
  [DS-LC6]    ST USBLC6-2SC6: 1 I/O1, 2 GND, 3 I/O2, 4 I/O2, 5 VBUS, 6 I/O1 (pins 1/6 and 3/4 are the two lines).
  [DS-HT75]   Holtek HT75xx-1 rev 1.50 SOT-89: 1 GND, 2 VIN, 3 VOUT; VIN max 24 V, Pd 250 mW.
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  [BH-18650]  MYOUNG BH-18650-B1BA002 drawing WD-CP-0088 (LCSC C2988620): '+' contact at the peg-hole end = pad 2,
              '-' = pad 1 (numbering of JLC's EasyEDA model, so the CPL fit by pin number keeps the peg in its hole).
  [KICAD]     KiCad library conventions: diode/LED pad 1 = cathode; SolderJumper "Bridged12" = pads 1-2 shorted by copper.
  [FW]        Bassberry firmware/OS pin map (docs/architecture.md): supervisor CH32V003 PC0 BOOST_EN, PC3..PC7 buttons,
              PD0 PI_POWEROFF, PD2/PD3/PD4 encoder A/B/switch, PD5 PI_IRQ, PD6 PI_SHUTDOWN_REQ, PA1 PI_PWR_EN, PA2 VBAT_SENSE;
              Pi GPIO4 = PDN amp 1, GPIO5 = PDN amp 2, GPIO17 = PI_IRQ, GPIO22 = shutdown request, GPIO27 = power-off ack.
  [BMS]       generic 3S BMS module, wire pads in order B-, B1, B2, B+, P- (module silk; physical check).
"""

# ---------------------------------------------------------------- pin tables (function name -> pad number)
PI_J8 = {  # [RPI-SCH] J8
    "3V3_1": "1", "5V_2": "2", "GPIO2": "3", "5V_4": "4", "GPIO3": "5", "GND_6": "6", "GPIO4": "7", "GPIO14": "8",
    "GND_9": "9", "GPIO15": "10", "GPIO17": "11", "GPIO18": "12", "GPIO27": "13", "GND_14": "14", "GPIO22": "15",
    "GPIO23": "16", "3V3_17": "17", "GPIO24": "18", "GPIO10": "19", "GND_20": "20", "GPIO9": "21", "GPIO25": "22",
    "GPIO11": "23", "GPIO8": "24", "GND_25": "25", "GPIO7": "26", "ID_SD": "27", "ID_SC": "28", "GPIO5": "29",
    "GND_30": "30", "GPIO6": "31", "GPIO12": "32", "GPIO13": "33", "GND_34": "34", "GPIO19": "35", "GPIO16": "36",
    "GPIO26": "37", "GPIO20": "38", "GND_39": "39", "GPIO21": "40",
}
PI_GND = [k for k in PI_J8 if k.startswith("GND_")]
PI_ROLE = {"GPIO2": "SDA1", "GPIO3": "SCL1", "GPIO14": "TXD0", "GPIO15": "RXD0",           # [RPI-SCH] labels
           "GPIO18": "PCM_CLK", "GPIO19": "PCM_FS", "GPIO21": "PCM_DOUT", "GPIO20": "PCM_DIN"}  # [BCM2711] ALT0
TAS = {"DGND1": "1", "DVDD": "2", "ADR": "3", "VR_DIG": "4", "DGND5": "5", "LRCLK": "6", "SCLK": "7", "SDIN": "8",
       "SDOUT": "9", "SDA": "10", "SCL": "11", "PDN": "12", "AVDD": "13", "AGND": "14", "PVDD15": "15", "PVDD16": "16",
       "OUT_B+": "17", "BST_B+": "18", "PGND19": "19", "OUT_B-": "20", "BST_B-": "21", "BST_A-": "22", "OUT_A-": "23",
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IP = {"TEST2": "1", "TEST3": "2", "TEST4": "3", "TEST5": "4", "VBUS": "5", "VBUSG": "6", "VBUSI": "7", "VIO": "8",
      "CSP1": "9", "CSN1": "10", "PCIN": "11", "HG1": "12", "BST1": "13", "LX1": "14", "LG1": "15", "LG2": "16",
      "LX2": "17", "BST2": "18", "HG2": "19", "PCON": "20", "CSN2": "21", "CSP2": "22", "BAT": "23", "CC_BDO": "24",
      "VCC5V": "25", "AGND": "26", "GPIO4": "27", "VCCIO": "28", "GPIO3": "29", "GPIO2": "30", "GPIO1": "31",
      "GPIO0": "32", "EN": "33", "CC2": "34", "DPC": "35", "DMC": "36", "CC1": "37", "GPIO19": "38", "GPIO20": "39",
      "TEST1": "40", "GND": "41"}                                                       # [DS-IP2366] 6.1
TPS = {"GND": "1", "SW": "2", "VIN": "3", "VFB": "4", "EN": "5", "VBST": "6"}            # [DS-TPS]
MT = {"SW": "1", "GND": "2", "FB": "3", "EN": "4", "IN": "5", "NC": "6"}                 # [DS-MT3608]
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DMMT = {"C1": "1", "B1": "2", "B2": "3", "C2": "4", "E2": "5", "E1": "6"}                # [DS-DMMT]
NMOS8 = {"S": "1", "S2": "2", "S3": "3", "G": "4", "D": "5"}                             # SO-8FL / TDSON-8 (JEDEC power SO-8)
EEP = {"A0": "1", "A1": "2", "A2": "3", "VSS": "4", "SDA": "5", "SCL": "6", "WP": "7", "VCC": "8"}   # [HAT-DG] eeprom-circuit
CH32 = {"PD4": "1", "PD5": "2", "PD6": "3", "PD7": "4", "PA1": "5", "PA2": "6", "VSS": "7", "PD0": "8", "VDD": "9",
        "PC0": "10", "PC1": "11", "PC2": "12", "PC3": "13", "PC4": "14", "PC5": "15", "PC6": "16", "PC7": "17",
        "PD1": "18", "PD2": "19", "PD3": "20"}                                           # [DS-CH32] Table 2-1 TSSOP20
CH340 = {"GND": "1", "TXD": "2", "RXD": "3", "V3": "4", "UD+": "5", "UD-": "6", "R232": "15", "VCC": "16"}  # [DS-CH340]
LC6 = {"IO1": "1", "GND": "2", "IO2": "3", "IO2b": "4", "VBUS": "5", "IO1b": "6"}        # [DS-LC6]
HT75 = {"GND": "1", "VIN": "2", "VOUT": "3"}                                             # [DS-HT75]
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    ("pulldown", ("Q101", "G"), 47000, "ZVD: 47 k gate to GND"),
    ("diff", [("Q101", "D"), ("Q101", "S"), ("Q101", "G")], "ZVD PFET pins on three different nodes"),
    # ================= I2S / I2C / control from the Pi [BCM2711] [FW]
    ("walk", PI("GPIO18"), U1("SCLK"), 1, "PCM_CLK -> amp 1 SCLK"), ("walk", PI("GPIO18"), U2("SCLK"), 1, "PCM_CLK -> amp 2 SCLK"),
    ("walk", PI("GPIO19"), U1("LRCLK"), 1, "PCM_FS -> amp 1 LRCLK"), ("walk", PI("GPIO19"), U2("LRCLK"), 1, "PCM_FS -> amp 2 LRCLK"),
    ("walk", PI("GPIO21"), U1("SDIN"), 1, "PCM_DOUT -> amp 1 SDIN"),
    ("walk", PI("GPIO21"), U2("SDIN"), 1, "PCM_DOUT -> amp 2 SDIN (JP201 default 1-2)"),
    ("same", [U1("SDOUT"), ("JP201", "3")], "amp 1 SDOUT on the JP201 alternative input of amp 2"),
    ("diff", [PI("GPIO18"), PI("GPIO19"), PI("GPIO21")], "I2S lines separate"),
    ("float", PI("GPIO20"), "PCM_DIN unused"),
    ("same", [PI("GPIO2"), U1("SDA"), U2("SDA"), MCU("PC1"), ("J502", "4")], "SDA1: amps, supervisor PC1 (I2C SDA), OLED"),
    ("same", [PI("GPIO3"), U1("SCL"), U2("SCL"), MCU("PC2"), ("J502", "3")], "SCL1: amps, supervisor PC2 (I2C SCL), OLED"),
    ("diff", [PI("GPIO2"), PI("GPIO3")], "SDA/SCL separate"),
    ("same", [PI("GPIO4"), U1("PDN")], "GPIO4 -> amp 1 PDN"),
    ("same", [PI("GPIO5"), U2("PDN")], "GPIO5 -> amp 2 PDN (one GPIO per codec for the Linux driver)"),
    ("pulldown", U1("PDN"), 10000, "amp 1 held in shutdown until the driver (deviation from TI 10 k pull-up: accepted)"),
    ("pulldown", U2("PDN"), 10000, "amp 2 held in shutdown until the driver"),
    ("walk", PI("GPIO14"), ("U502", "RXD"), 1, "TXD0 -> USB console RXD"),
    ("walk", PI("GPIO15"), ("U502", "TXD"), 1, "USB console TXD -> RXD0"),
    ("same", [PI("GPIO17"), MCU("PD5")], "PI_IRQ: supervisor PD5 -> GPIO17"),
    ("same", [PI("GPIO22"), MCU("PD6")], "shutdown request: supervisor PD6 -> GPIO22"),
    ("same", [PI("GPIO27"), MCU("PD0")], "power-off ack: GPIO27 -> supervisor PD0"),
    ("float", PI("GPIO6"), "GPIO6 unused (HAT guide: not driven at boot)"),
    ("float", PI("GPIO16"), "GPIO16 unused (HAT guide: not driven at boot)"),
    # ================= amplifiers [DS-TAS]
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    ("cap", IC("CSN2"), IC("BAT"), 1e-6, 0.1, "1 uF CSN2-BAT"),
    ("same", [IC("BAT"), IC("CSP2"), ("F401", "2")], "BAT = CSP2 = fused pack +"),
    ("cap", IC("VCC5V"), ("GND", None), 2.2e-6, 0.1, "VCC5V 2.2 uF"), ("cap", IC("VCCIO"), ("GND", None), 2.2e-6, 0.1, "VCCIO 2.2 uF"),
    ("pulldown", IC("GPIO4"), 6200, "BAT_NUM 6.2 k = 3 cells in series"),
    ("pulldown", IC("GPIO2"), 9100, "VSET 9.1 k = 4.2 V per cell"),
    ("pulldown", IC("GPIO3"), 3600, "PSET 3.6 k = 30 W"),
    ("same", [IC("GPIO0"), ("J402", "1")], "NTC pin to the cell thermistor connector"),
    ("pulldown", IC("EN"), 10000, "EN 10 k to GND"),
    ("same", [IC("CC1"), ("J301", "CC1")], "CC1"), ("same", [IC("CC2"), ("J301", "CC2")], "CC2"),
    ("diff", [("J301", "CC1"), ("J301", "CC2")], "CC1/CC2 separate"),
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    ("cap", ("U303", "VBST"), ("U303", "SW"), 0.1e-6, 0.1, "VBST 0.1 uF to SW"),
    ("gnd", [("U303", "GND")], "buck GND"),
    ("ratio", ("U303", "VFB"), ("Q101", "D"), 0.760, 5.0, 5.25, "Vout = 0.760*(1+Rtop/Rbot) for the Pi"),
    ("same", [("U303", "EN"), MCU("PA1")], "buck EN from supervisor PA1"),
    ("pulldown", ("U303", "EN"), 100000, "buck EN default off"),
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

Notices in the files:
hardware/bassberry/audio.kicad_sch:
Z2Labs - Bassberry (open hardware, CERN-OHL-S-2.0)
hardware/bassberry/bassberry.kicad_pcb:
Z2Labs - CERN-OHL-S-2.0
